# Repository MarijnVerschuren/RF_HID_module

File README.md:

# RF_HID_module
A simple RF and HID test device based on the CH592F RISCV processor

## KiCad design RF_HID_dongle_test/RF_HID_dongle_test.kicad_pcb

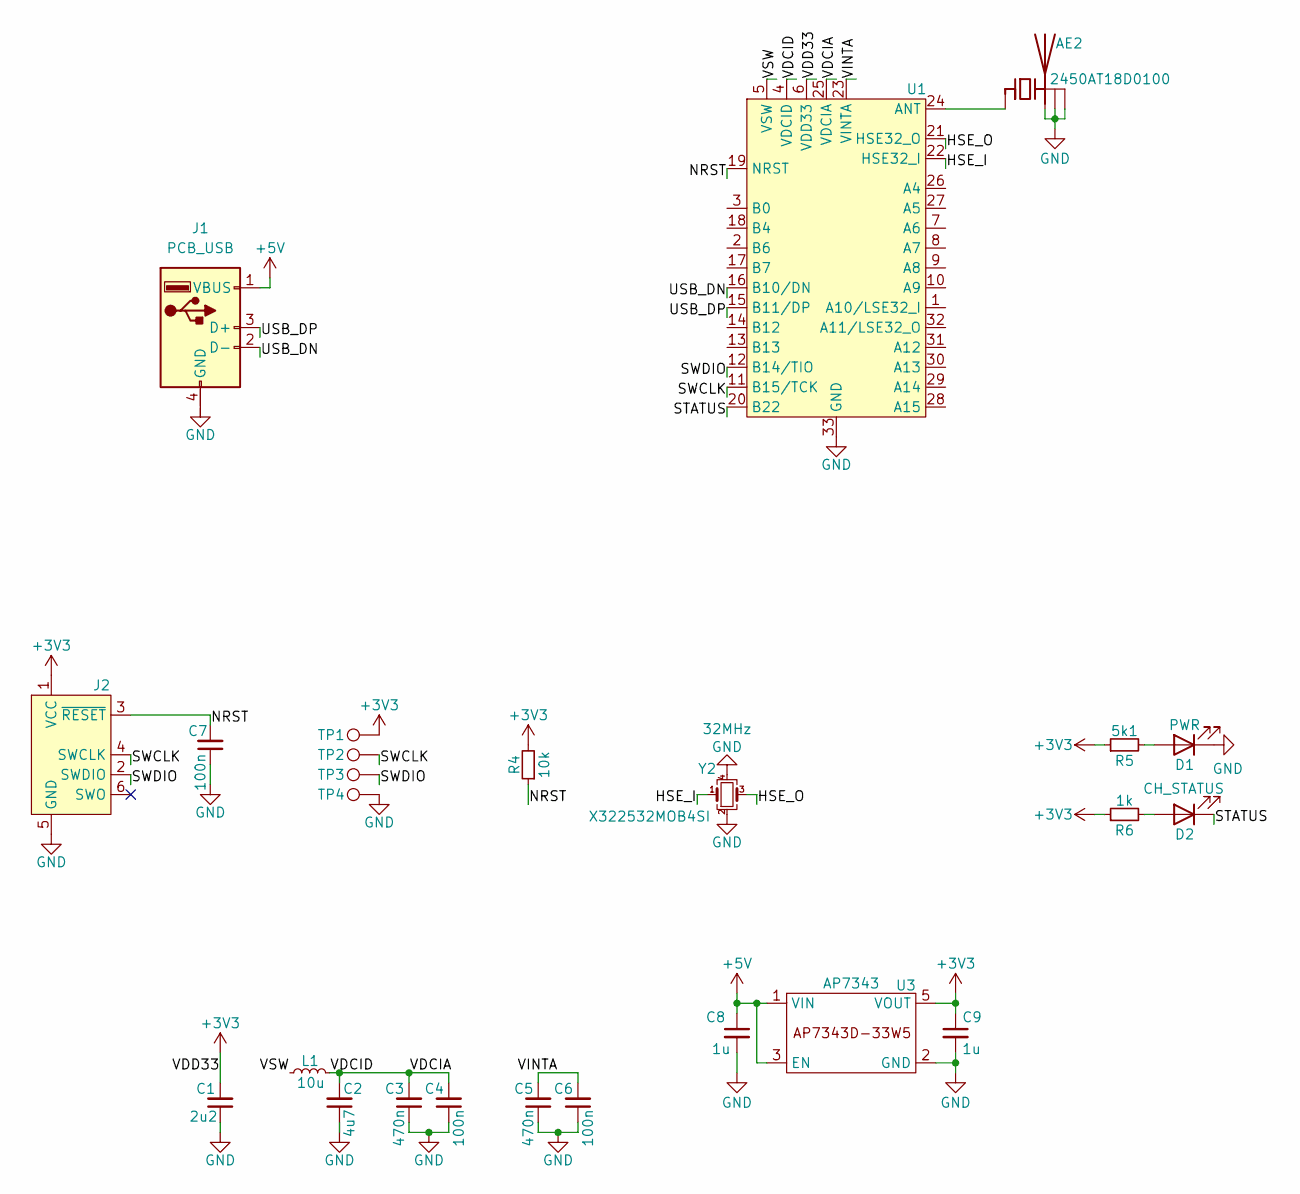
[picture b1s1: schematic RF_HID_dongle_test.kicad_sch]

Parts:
AE2: 2450AT18D0100
C1: 2u2; C_0603_1608Metric
C2: 4u7; C_0603_1608Metric
C3, C5: 470n; C_0603_1608Metric
C4, C6, C7: 100n; C_0603_1608Metric
C8, C9: 1u; C_0603_1608Metric; LCSC C14445
D1: PWR; LED_0603_1608Metric; mouser 710-150060RS75000
D2: CH_STATUS; LED_0603_1608Metric; mouser 710-150060BS75000
J1: PCB_USB
J2: Conn_ARM_SWD_TagConnect_TC2030; Tag-Connect_TC2030-IDC-FP_2x03_P1.27mm_Vertical
L1: 10u; L_0805_2012Metric
R4: 10k; R_0603_1608Metric
R5: 5k1; R_0603_1608Metric; mouser 791-RMC1/16-512JTP
R6: 1k; R_0603_1608Metric; mouser 71-CRCW06031K00FKEE
TP1, TP2, TP3, TP4: TestPoint; TestPoint_Pad_D1.0mm
U1: QFN-32-1EP_4x4mm_P0.4mm_EP2.65x2.65mm
U3: AP7343; SOT-25
Y2: 32MHz; Crystal_SMD_3225-4Pin_3.2x2.5mm

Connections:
+3V3: C1.2, C9.1, J2.1 (VCC), R4.2, R5.1, R6.1, TP1.1, U1.6 (VDD33), U3.5 (VOUT)
+5V: C8.1, J1.1 (VBUS), U3.1 (VIN), U3.3 (EN)
/HSE_I: U1.22 (HSE32_I), Y2.1
/HSE_O: U1.21 (HSE32_O), Y2.3
/NRST: C7.2, J2.3 (~RESET), R4.1, U1.19 (NRST)
/STATUS: D2.1 (K), U1.20 (B22)
/SWCLK: J2.4 (SWCLK), TP2.1, U1.11 (B15/TCK)
/SWDIO: J2.2 (SWDIO), TP3.1, U1.12 (B14/TIO)
/USB_DN: J1.2 (D-), U1.16 (B10/DN)
/USB_DP: J1.3 (D+), U1.15 (B11/DP)
/VDCIA: C2.2, C3.2, C4.2, L1.2, U1.4 (VDCID), U1.25 (VDCIA)
/VINTA: C5.2, C6.2, U1.23 (VINTA)
/VSW: L1.1, U1.5 (VSW)
GND: AE2.2, AE2.3, AE2.4, C1.1, C2.1, C3.1, C4.1, C5.1, C6.1, C7.1, C8.2, C9.2, D1.1 (K), J1.4 (GND), J2.5 (GND), TP4.1, U1.33 (GND), U3.2 (GND), Y2.2, Y2.4
unnamed: AE2.1 (FEED), U1.24 (ANT)
unnamed: D1.2 (A), R5.2
unnamed: D2.2 (A), R6.2

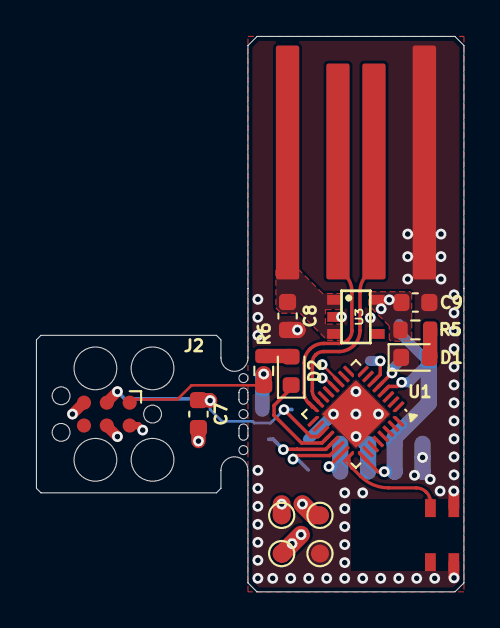
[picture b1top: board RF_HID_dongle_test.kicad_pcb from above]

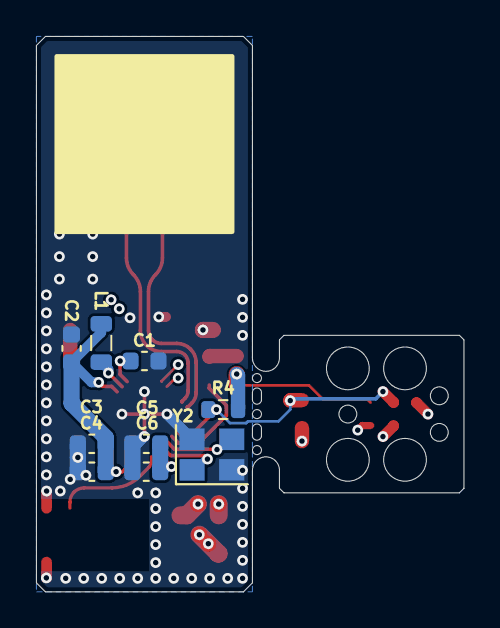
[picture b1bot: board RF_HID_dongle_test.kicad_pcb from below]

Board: 4 copper layers, 23.8 x 30.9 mm, 25 parts (9 on the bottom side), 17 nets.

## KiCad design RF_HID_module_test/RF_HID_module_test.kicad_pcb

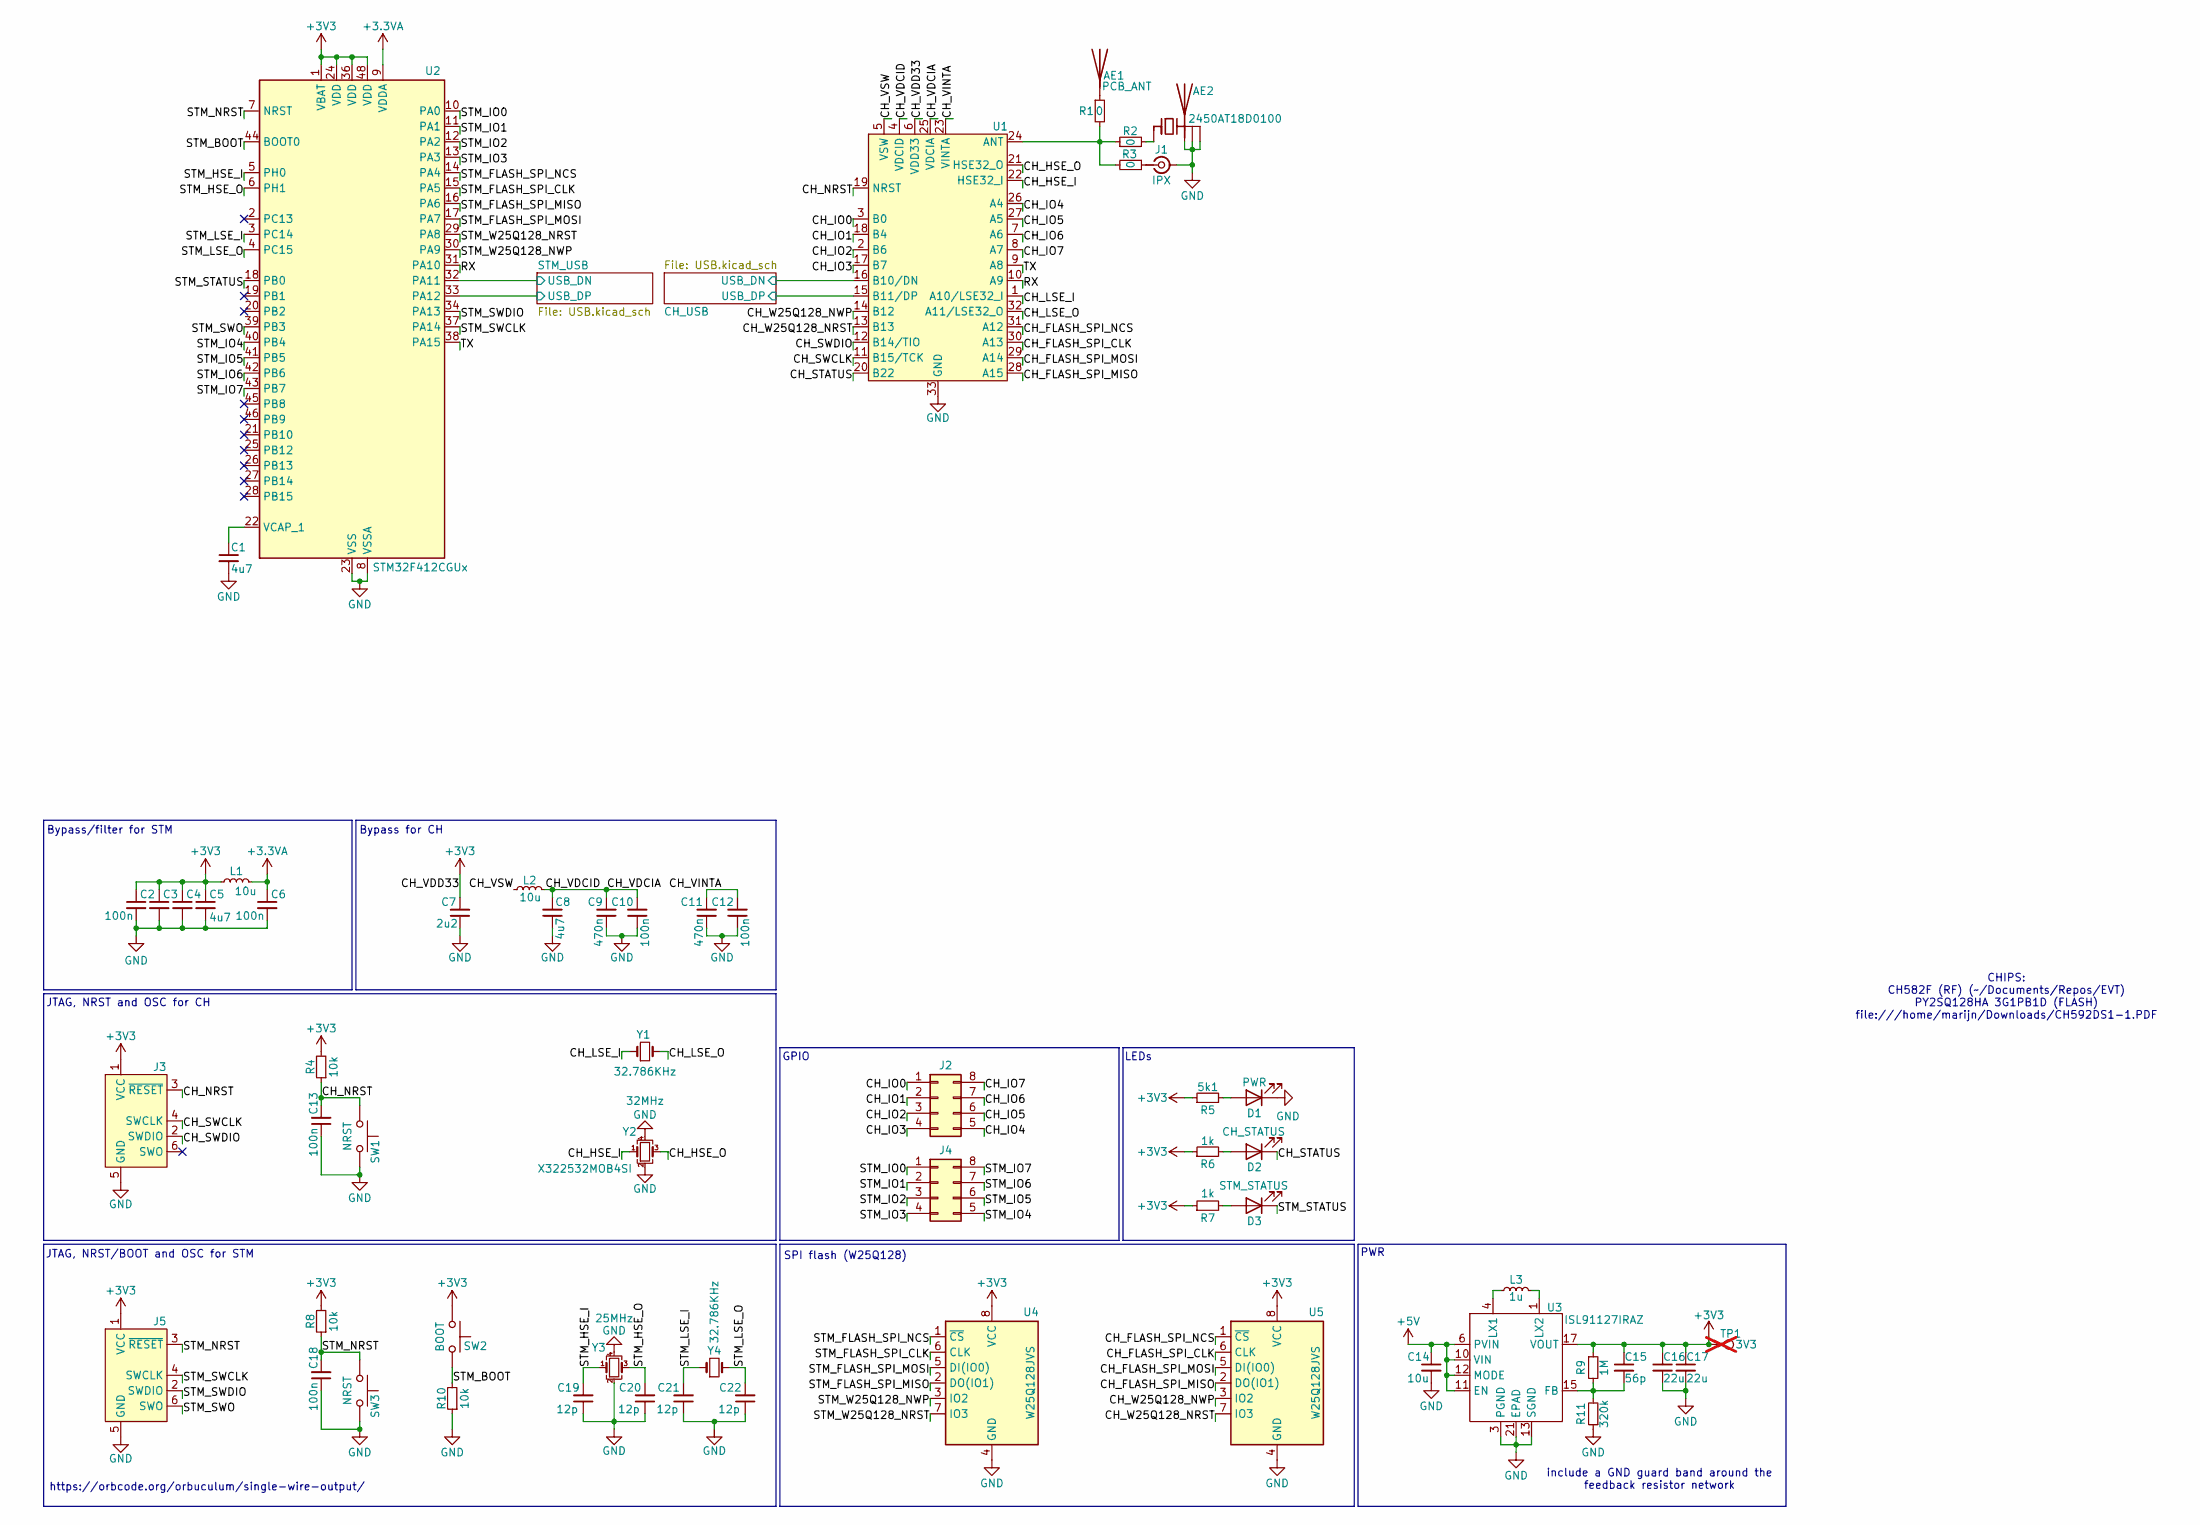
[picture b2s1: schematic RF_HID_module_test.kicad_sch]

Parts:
AE1: PCB_ANT; Texas_SWRA117D_2.4GHz_Left
AE2: 2450AT18D0100
C1: 4u7; C_0603_1608Metric; LCSC C12530
C2, C3, C4, C6, C10, C12, C13, C18: 100n; C_0603_1608Metric
C5, C8: 4u7; C_0603_1608Metric
C7: 2u2; C_0603_1608Metric
C9, C11: 470n; C_0603_1608Metric
C14: 10u; C_0603_1608Metric; mouser 187-CL10A106MQ8NNND
C15: 56p; C_0603_1608Metric; mouser 187-CL10A226MP8NUNE
C16, C17: 22u; C_0603_1608Metric; mouser 187-CL10A226MP8NUNE
C19, C20, C21, C22: 12p; C_0603_1608Metric
D1: PWR; LED_0603_1608Metric; mouser 710-150060RS75000
D2: CH_STATUS; LED_0603_1608Metric; mouser 710-150060BS75000
D3: STM_STATUS; LED_0603_1608Metric; mouser 710-150060BS75000
J1: IPX; U.FL_Molex_MCRF_73412-0110_Vertical
J2, J4: Conn_02x04_Counter_Clockwise; PinSocket_2x04_P2.54mm_Vertical
J3, J5: Conn_ARM_SWD_TagConnect_TC2030; Tag-Connect_TC2030-IDC-FP_2x03_P1.27mm_Vertical
L1, L2: 10u; L_0805_2012Metric
L3: 1u; L_APV_ANR4018; mouser 963-NRS4018T1R0NDGJ
R1, R2, R3: 0; R_0603_1608Metric; LCSC C25118
R4, R8, R10: 10k; R_0603_1608Metric
R5: 5k1; R_0603_1608Metric; mouser 791-RMC1/16-512JTP
R6, R7: 1k; R_0603_1608Metric; mouser 71-CRCW06031K00FKEE
R9: 1M; R_0603_1608Metric; mouser 791-RMC1/16-512JTP
R11: 320k; R_0603_1608Metric; mouser 791-RMC1/16-512JTP
SW1, SW3: NRST; SW_SPST_PTS810; LCSC C2681476
SW2: BOOT; SW_SPST_PTS810; LCSC C2681476
TP1: 3V3; TestPoint_Pad_D1.5mm; not fitted
U1: QFN-32-1EP_4x4mm_P0.4mm_EP2.65x2.65mm
U2: STM32F412CGUx; QFN-48-1EP_7x7mm_P0.5mm_EP5.6x5.6mm
U3: ISL91127IRAZ; QFN-20-1EP_4x4mm_P0.5mm_EP2.7x2.7mm_ThermalVias; mouser 968-ISL91127IRAZ-T
U4, U5: W25Q128JVS; SOIC-8_W25QxJVS
Y1, Y4: 32.786KHz; Crystal_SMD_3215-2Pin_3.2x1.5mm
Y2: 32MHz; Crystal_SMD_3225-4Pin_3.2x2.5mm
Y3: 25MHz; Crystal_SMD_3225-4Pin_3.2x2.5mm

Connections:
+3.3VA: C6.1, L1.2, U2.9 (VDDA)
+3V3: C2.1, C3.1, C4.1, C5.1, C7.2, C15.1, C16.1, C17.1, J3.1 (VCC), J5.1 (VCC), L1.1, R4.2, R5.1, R6.1, R7.1, R8.2, R9.1, SW2.1, TP1.1, U1.6 (VDD33), U2.1 (VBAT), U2.24 (VDD), U2.36 (VDD), U2.48 (VDD), U3.17 (VOUT), U3.18 (VOUT), U3.19 (VOUT), U3.20 (VOUT), U4.8 (VCC), U5.8 (VCC)
+5V: C14.1, U3.6 (PVIN), U3.7 (PVIN), U3.8 (PVIN), U3.9 (PVIN), U3.10 (VIN), U3.11 (EN), U3.12 (MODE); also elsewhere on the board
/CH_FLASH_SPI_CLK: U1.30 (A13), U5.6 (CLK)
/CH_FLASH_SPI_MISO: U1.28 (A15), U5.2 (DO(IO1))
/CH_FLASH_SPI_MOSI: U1.29 (A14), U5.5 (DI(IO0))
/CH_FLASH_SPI_NCS: U1.31 (A12), U5.1 (~CS)
/CH_HSE_I: U1.22 (HSE32_I), Y2.1
/CH_HSE_O: U1.21 (HSE32_O), Y2.3
/CH_IO0: J2.1, U1.3 (B0)
/CH_IO1: J2.2, U1.18 (B4)
/CH_IO2: J2.3, U1.2 (B6)
/CH_IO3: J2.4, U1.17 (B7)
/CH_IO4: J2.5, U1.26 (A4)
/CH_IO5: J2.6, U1.27 (A5)
/CH_IO6: J2.7, U1.7 (A6)
/CH_IO7: J2.8, U1.8 (A7)
/CH_LSE_I: U1.1 (A10/LSE32_I), Y1.1
/CH_LSE_O: U1.32 (A11/LSE32_O), Y1.2
/CH_NRST: C13.2, J3.3 (~RESET), R4.1, SW1.1, U1.19 (NRST)
/CH_STATUS: D2.1 (K), U1.20 (B22)
/CH_SWCLK: J3.4 (SWCLK), U1.11 (B15/TCK)
/CH_SWDIO: J3.2 (SWDIO), U1.12 (B14/TIO)
/CH_USB/USB_DN: U1.16 (B10/DN); also elsewhere on the board
/CH_USB/USB_DP: U1.15 (B11/DP); also elsewhere on the board
/CH_VDCIA: C8.2, C9.2, C10.2, L2.2, U1.4 (VDCID), U1.25 (VDCIA)
/CH_VINTA: C11.2, C12.2, U1.23 (VINTA)
/CH_VSW: L2.1, U1.5 (VSW)
/CH_W25Q128_NRST: U1.13 (B13), U5.7 (IO3)
/CH_W25Q128_NWP: U1.14 (B12), U5.3 (IO2)
/RX: U1.10 (A9), U2.31 (PA10)
/STM_BOOT: R10.2, SW2.2, U2.44 (BOOT0)
/STM_FLASH_SPI_CLK: U2.15 (PA5), U4.6 (CLK)
/STM_FLASH_SPI_MISO: U2.16 (PA6), U4.2 (DO(IO1))
/STM_FLASH_SPI_MOSI: U2.17 (PA7), U4.5 (DI(IO0))
/STM_FLASH_SPI_NCS: U2.14 (PA4), U4.1 (~CS)
/STM_HSE_I: C19.2, U2.5 (PH0), Y3.1
/STM_HSE_O: C20.2, U2.6 (PH1), Y3.3
/STM_IO0: J4.1, U2.10 (PA0)
/STM_IO1: J4.2, U2.11 (PA1)
/STM_IO2: J4.3, U2.12 (PA2)
/STM_IO3: J4.4, U2.13 (PA3)
/STM_IO4: J4.5, U2.40 (PB4)
/STM_IO5: J4.6, U2.41 (PB5)
/STM_IO6: J4.7, U2.42 (PB6)
/STM_IO7: J4.8, U2.43 (PB7)
/STM_LSE_I: C21.2, U2.3 (PC14), Y4.1
/STM_LSE_O: C22.2, U2.4 (PC15), Y4.2
/STM_NRST: C18.2, J5.3 (~RESET), R8.1, SW3.1, U2.7 (NRST)
/STM_STATUS: D3.1 (K), U2.18 (PB0)
/STM_SWCLK: J5.4 (SWCLK), U2.37 (PA14)
/STM_SWDIO: J5.2 (SWDIO), U2.34 (PA13)
/STM_SWO: J5.6 (SWO), U2.39 (PB3)
/STM_USB/USB_DN: U2.32 (PA11); also elsewhere on the board
/STM_USB/USB_DP: U2.33 (PA12); also elsewhere on the board
/STM_W25Q128_NRST: U2.29 (PA8), U4.7 (IO3)
/STM_W25Q128_NWP: U2.30 (PA9), U4.3 (IO2)
/TX: U1.9 (A8), U2.38 (PA15)
GND: AE1.2, AE2.2, AE2.3, AE2.4, C1.2, C2.2, C3.2, C4.2, C5.2, C6.2, C7.1, C8.1, C9.1, C10.1, C11.1, C12.1, C13.1, C14.2, C16.2, C17.2, C18.1, C19.1, C20.1, C21.1, C22.1, D1.1 (K), J1.2 (Ext), J3.5 (GND), J5.5 (GND), R10.1, R11.1, SW1.2, SW3.2, U1.33 (GND), U2.8 (VSSA), U2.23 (VSS), U2.35 (VSS), U2.47 (VSS), U2.49 (VSS), U3.3 (PGND), U3.13 (SGND), U3.14 (SGND), U3.21 (EPAD), U4.4 (GND), U5.4 (GND), Y2.2, Y2.4, Y3.2, Y3.4; also elsewhere on the board
unnamed: AE1.1 (A), R1.1
unnamed: AE2.1 (FEED), R2.2
unnamed: D1.2 (A), R5.2
unnamed: D2.2 (A), R6.2
unnamed: D3.2 (A), R7.2
unnamed: J1.1 (In), R3.1
unnamed: L3.1, U3.4 (LX1), U3.5 (LX1)
unnamed: L3.2, U3.1 (LX2), U3.2 (LX2)
unnamed: R1.2, R2.1, R3.2, U1.24 (ANT)
unnamed: C1.1, U2.22 (VCAP_1)
unnamed: C15.2, R9.2, R11.2, U3.15 (FB)

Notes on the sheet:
LEDs
Bypass/filter for STM
JTAG, NRST and OSC for CH
JTAG, NRST/BOOT and OSC for STM
SPI flash (W25Q128)
CHIPS: CH582F (RF) (~/Documents/Repos/EVT) PY2SQ128HA 3G1PB1D (FLASH) file:///home/marijn/Downloads/CH592DS1-1.PDF
PWR
GPIO
https://orbcode.org/orbuculum/single-wire-output/
include a GND guard band around the feedback resistor network
Bypass for CH

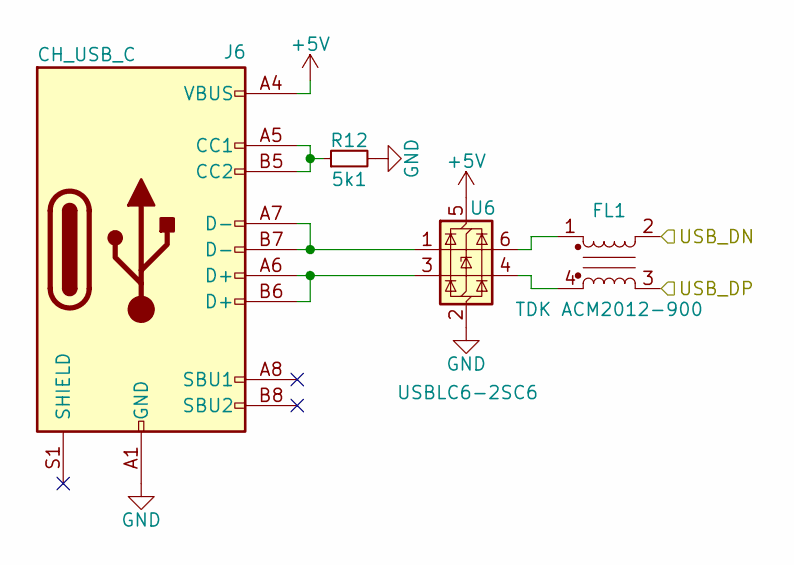
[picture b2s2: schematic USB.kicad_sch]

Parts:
FL1: TDK ACM2012-900; ACM2012_900_2P_T002_Correct; LCSC C19972
J6: CH_USB_C; USB_C_Receptacle_HCTL_HC-TYPE-C-16P-01A
R12: 5k1; R_0603_1608Metric
U6: USBLC6-2SC6; SOT-23-6; LCSC C2827654

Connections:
+5V: J6.A4 (VBUS), J6.A9 (VBUS), J6.B4 (VBUS), J6.B9 (VBUS), U6.5 (VBUS); also elsewhere on the board
/STM_USB/USB_DN: FL1.2; also elsewhere on the board
/STM_USB/USB_DP: FL1.3; also elsewhere on the board
GND: J6.A1 (GND), J6.A12 (GND), J6.B1 (GND), J6.B12 (GND), R12.2, U6.2 (GND); also elsewhere on the board
unnamed: FL1.1, U6.6 (I/O1)
unnamed: FL1.4, U6.4 (I/O2)
unnamed: J6.A5 (CC1), J6.B5 (CC2), R12.1
unnamed: J6.A6 (D+), J6.B6 (D+), U6.3 (I/O2)
unnamed: J6.A7 (D-), J6.B7 (D-), U6.1 (I/O1)

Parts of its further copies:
FL2: TDK ACM2012-900; ACM2012_900_2P_T002_Correct; LCSC C19972
J7: CH_USB_C; USB_C_Receptacle_HCTL_HC-TYPE-C-16P-01A
R13: 5k1; R_0603_1608Metric
U7: USBLC6-2SC6; SOT-23-6; LCSC C2827654

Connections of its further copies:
+5V: J7.A4 (VBUS), J7.A9 (VBUS), J7.B4 (VBUS), J7.B9 (VBUS), U7.5 (VBUS); also elsewhere on the board
/CH_USB/USB_DN: FL2.2; also elsewhere on the board
/CH_USB/USB_DP: FL2.3; also elsewhere on the board
GND: J7.A1 (GND), J7.A12 (GND), J7.B1 (GND), J7.B12 (GND), R13.2, U7.2 (GND); also elsewhere on the board
unnamed: FL2.1, U7.6 (I/O1)
unnamed: FL2.4, U7.4 (I/O2)
unnamed: J7.A5 (CC1), J7.B5 (CC2), R13.1
unnamed: J7.A6 (D+), J7.B6 (D+), U7.3 (I/O2)
unnamed: J7.A7 (D-), J7.B7 (D-), U7.1 (I/O1)

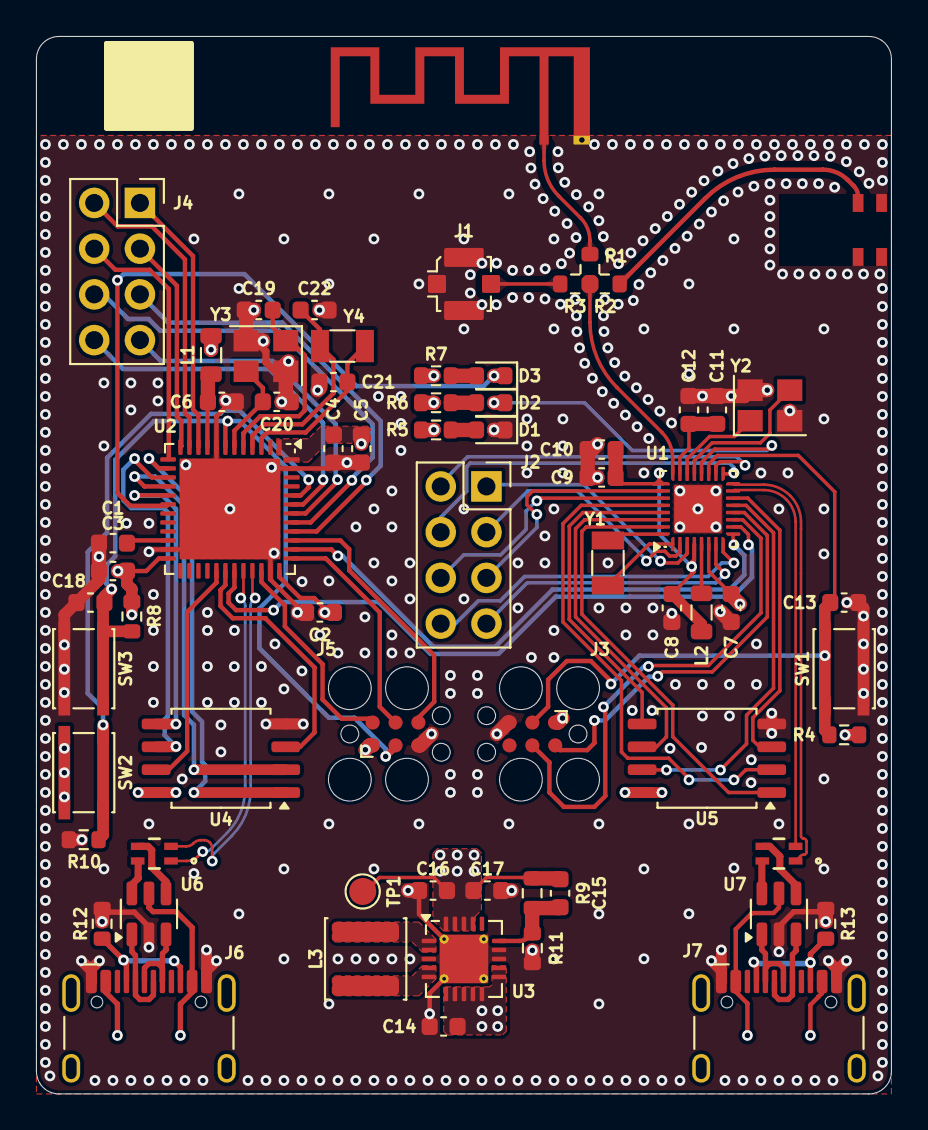
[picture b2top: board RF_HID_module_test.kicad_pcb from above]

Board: 4 copper layers, 47.5 x 58.8 mm, 67 parts (0 on the bottom side), 80 nets.

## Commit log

2025-03-07 Project init
2025-03-12 Schematic V0
2025-03-20 Layout V0
2025-03-26 RF dongle
2025-05-03 EOL for WCH chips
2025-05-03 Cleaned up gitignore
